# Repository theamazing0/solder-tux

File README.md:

# Tux for Solder

This is a model of Tux, the mascot of the Linux kernel. Tux loves it when people pat his head or rub his belly (clicking the buttons), but he HATES it when people do both at the same time. The PCB is a XOR gate that makes the LED light up only when Tux is happy. This is my first PCB.

## Parts

- 1x Battery Holder
- 2x Push Buttons
- 5x 1k Resistors
- 4x NPN Transistors
- 1x LED

## Screenshots

## Slack Username
`Samvid`

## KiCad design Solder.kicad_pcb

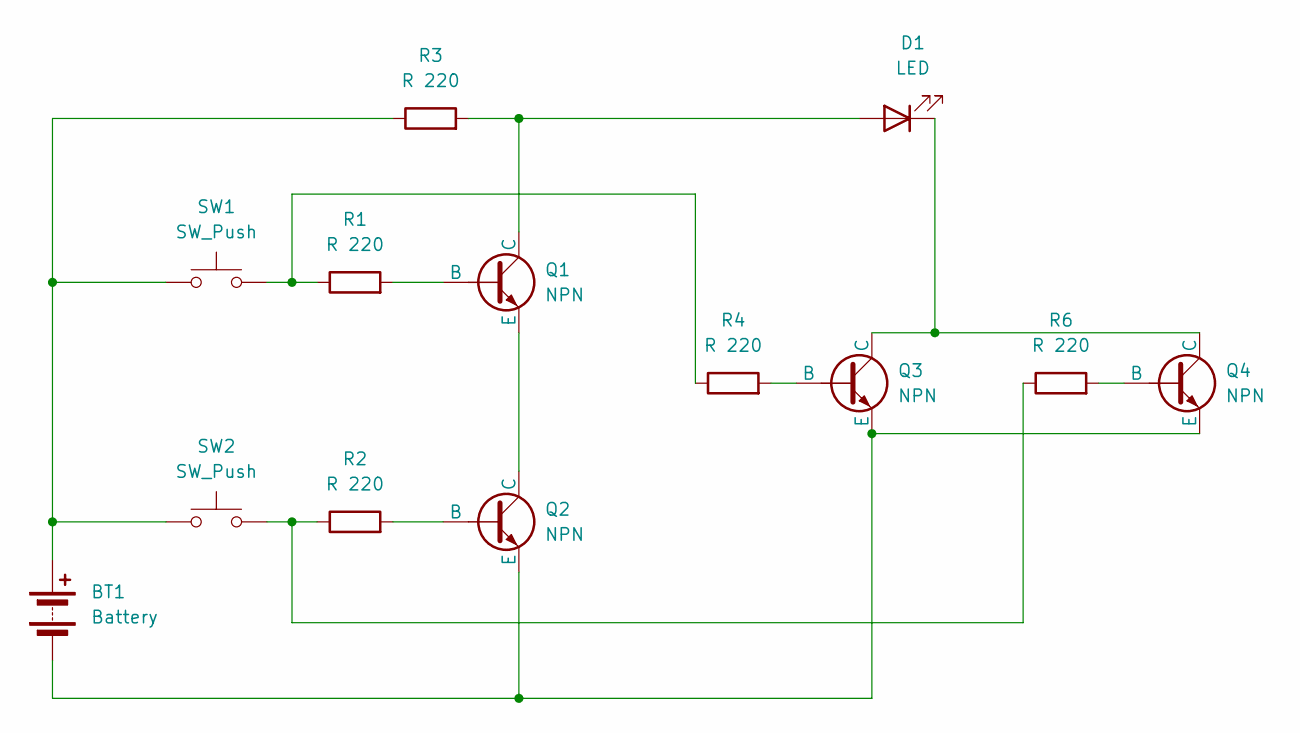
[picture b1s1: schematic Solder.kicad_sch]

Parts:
BT1: Battery; BatteryHolder_Keystone_3034_1x20mm
D1: LED; LED_D5.0mm
Q1, Q2, Q3, Q4: NPN; TO-92L_HandSolder
R1, R2, R3, R4, R6: R 220; R_Axial_DIN0207_L6.3mm_D2.5mm_P7.62mm_Horizontal
SW1, SW2: SW_Push; SW_PUSH_6mm

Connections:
unnamed: BT1.1 (+), R3.1, SW1.1, SW2.1
unnamed: BT1.2 (-), Q2.3 (E), Q3.3 (E), Q4.3 (E)
unnamed: D1.2 (A), Q1.1 (C), R3.2
unnamed: D1.1 (K), Q3.1 (C), Q4.1 (C)
unnamed: Q1.2 (B), R1.2
unnamed: Q1.3 (E), Q2.1 (C)
unnamed: Q2.2 (B), R2.2
unnamed: Q3.2 (B), R4.2
unnamed: Q4.2 (B), R6.2
unnamed: R1.1, R4.1, SW1.2
unnamed: R2.1, R6.1, SW2.2

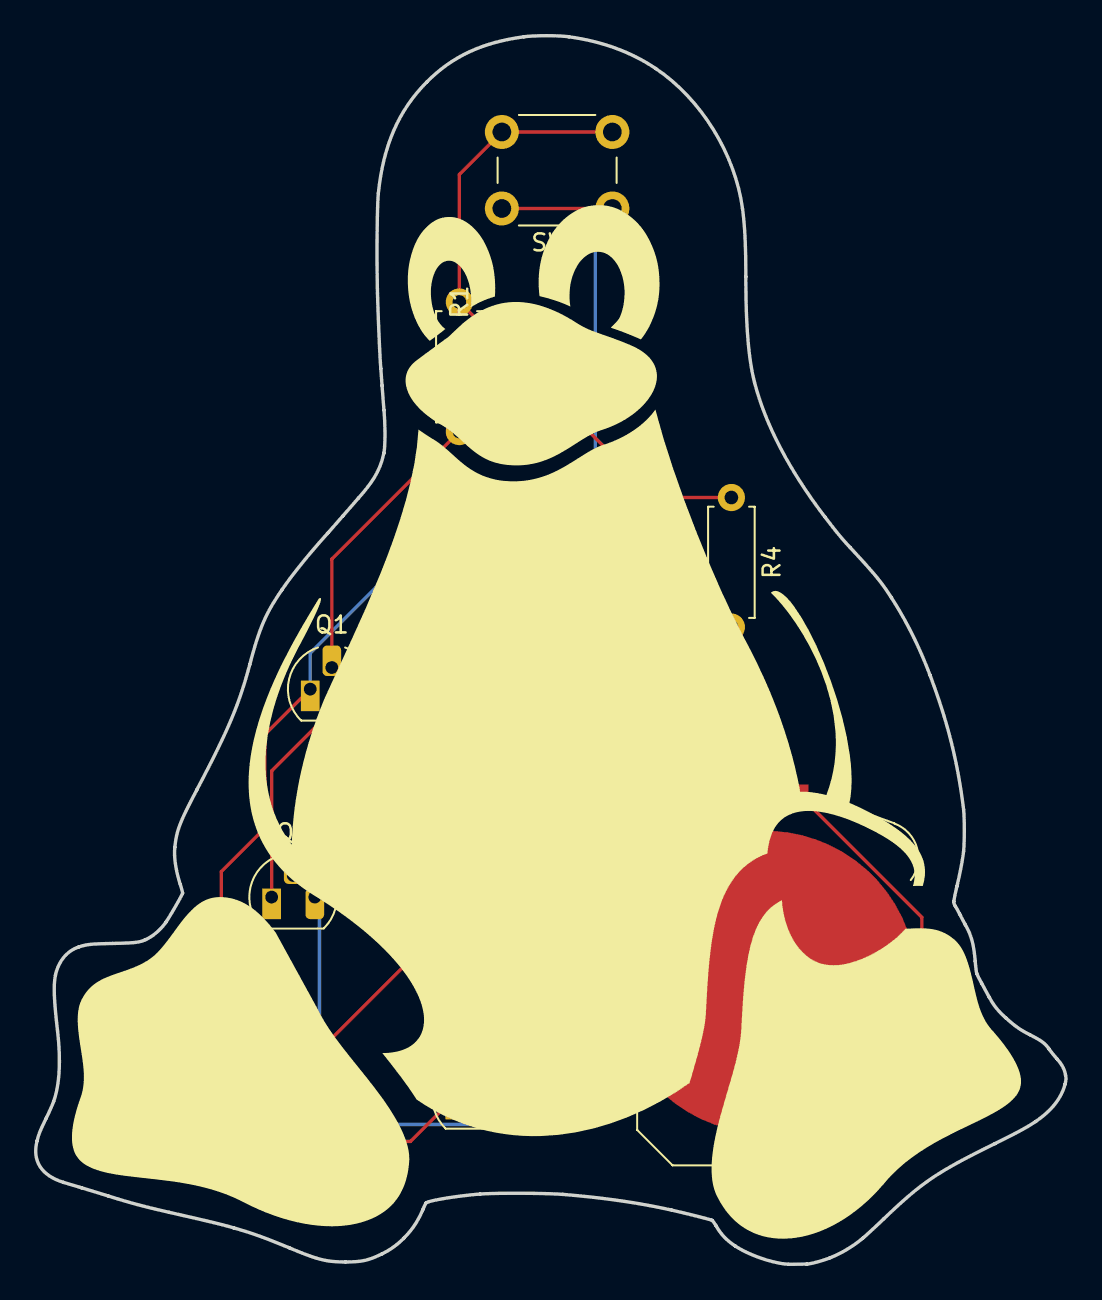
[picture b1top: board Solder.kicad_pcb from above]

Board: 2 copper layers, 60.6 x 72.3 mm, 13 parts (0 on the bottom side), 11 nets.

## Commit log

2025-05-03 added gerber and drill files
2025-05-03 add pics
2025-05-03 add pics to readme
2025-05-03 added logos to the back
